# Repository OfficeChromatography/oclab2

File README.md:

# OCLab2
## Next Generation Office Chromatography

The former [OCLab prototype](https://github.com/OfficeChromatography/OCLab) of a “miniaturized all-in-one open
 source system for planar chromatography” was upgraded by an HPTLC plate visualizing cabinet to protect the 
 plate from extraneous light during capturing of images, including RGBW, UV 278 nm and UV 366 nm LED boards 
 as well as a Raspberry Pi V2 camera module. 
 
 Additionally, a newly designed printhead was manufactured, 
 controlled by a self-constructed ink-jet board allowing to check the nozzles’ resistance heating circuit. 
 Furthermore, plate heating was enabled, especially favorable when higher volumes of aqueous samples are to 
 be applied. 
 
 The former [OC Manager software](https://github.com/OfficeChromatography/OC_manager) was completely 
 restructured and newly written in R to speed-up the processes ([OC_manager2](https://github.com/OfficeChromatography/oc_manager2))
 , also supported by the new Raspberry Pi 4B computer with 4 GB RAM .

### Hardware/Firmware
The 3D printed parts are in the folder 'Construction Set', the electronic boards are described in the folder 
'Eagle Files', and the modified firmware is available in the folder 'Marlin'.
Assembly instructions are in the folder 'Instruction'.

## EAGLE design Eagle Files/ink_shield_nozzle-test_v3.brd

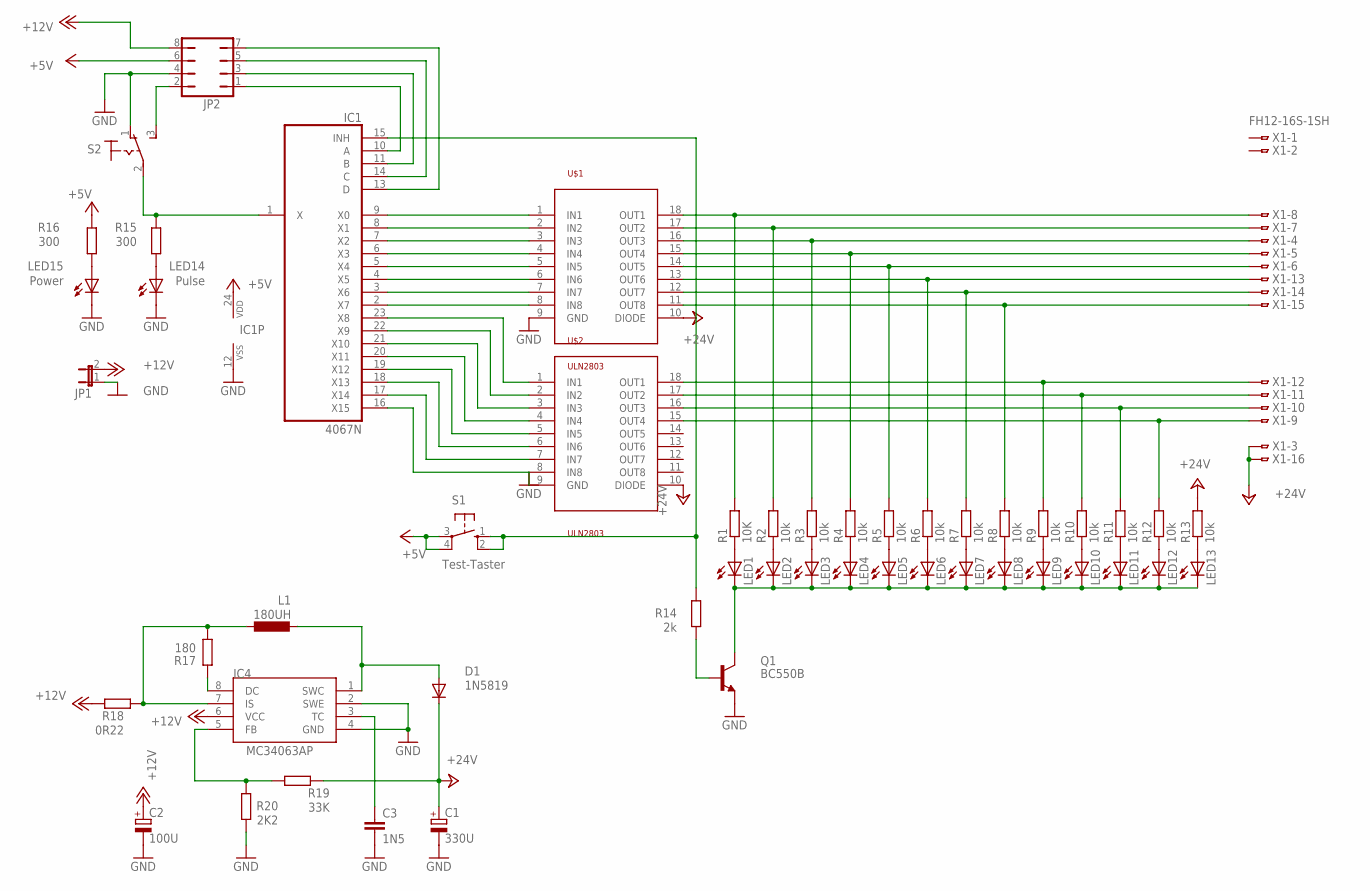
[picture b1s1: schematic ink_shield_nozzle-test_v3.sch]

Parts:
C1: 330U; E3,5-10
C2: 100U; E2,5-6
C3: 1N5; C025-024X044
D1: 1N5819; DO35-10
IC1: 4067N; DIL24-6
IC4: MC34063AP; DIL08
JP1: JP1E; JP1
JP2: JP4Q
L1: 180UH; 6000-XXXX-RC
LED1, LED2, LED3, LED4, LED5, LED6, LED7, LED8, LED9, LED10, LED11, LED12, LED13: LEDCHIPLED_0603; CHIPLED_0603
LED14: Pulse; LED3MM
LED15: Power; LED3MM
Q1: BC550B; TO92-EBC
R1: 10K; M1206
R2, R3, R4, R5, R6, R7, R8, R9, R10, R11, R12, R13: 10k; M1206
R14: 2k; M3216
R15, R16: 300; 0207/10
R17: 180; 0207/12
R18: 0R22; 0207/12
R19: 33K; 0207/12
R20: 2K2; 0207/10
S1: Test-Taster; B3F-10XX
S2: M9040P
U$1, U$2: ULN2803; SO18L
X1: FH12-16S-1SH

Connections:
+5V: IC1.24 (VDD), JP2.6, R16.2, S1.3, S1.4 (P1)
+12V: C2.+, IC4.6 (VCC), JP1.2, JP2.8, R18.2
+24V: C1.+, D1.C, R13.2, R19.1, U$1.10 (DIODE), U$2.10 (DIODE), X1.3, X1.16
GND: C1.-, C2.-, C3.2, IC1.12 (VSS), IC4.2 (SWE), IC4.4 (GND), JP1.1, JP2.4, LED14.K (C), LED15.K (C), Q1.E, R20.1, S2.1 (O), U$1.9 (GND), U$2.9 (GND)
unnamed: IC1.9 (X0), U$1.1 (IN1)
unnamed: IC1.8 (X1), U$1.2 (IN2)
unnamed: IC1.7 (X2), U$1.3 (IN3)
unnamed: IC1.6 (X3), U$1.4 (IN4)
unnamed: IC1.5 (X4), U$1.5 (IN5)
unnamed: IC1.4 (X5), U$1.6 (IN6)
unnamed: IC1.3 (X6), U$1.7 (IN7)
unnamed: IC1.2 (X7), U$1.8 (IN8)
unnamed: IC1.23 (X8), U$2.1 (IN1)
unnamed: IC1.22 (X9), U$2.2 (IN2)
unnamed: IC1.21 (X10), U$2.3 (IN3)
unnamed: IC1.20 (X11), U$2.4 (IN4)
unnamed: IC1.19 (X12), U$2.5 (IN5)
unnamed: IC1.18 (X13), U$2.6 (IN6)
unnamed: IC1.17 (X14), U$2.7 (IN7)
unnamed: IC1.16 (X15), U$2.8 (IN8)
unnamed: LED1.A, R1.1
unnamed: LED2.A, R2.1
unnamed: LED3.A, R3.1
unnamed: LED4.A, R4.1
unnamed: LED5.A, R5.1
unnamed: LED6.A, R6.1
unnamed: LED7.A, R7.1
unnamed: LED8.A, R8.1
unnamed: LED9.A, R9.1
unnamed: LED10.A, R10.1
unnamed: LED11.A, R11.1
unnamed: LED12.A, R12.1
unnamed: LED1.C, LED2.C, LED3.C, LED4.C, LED5.C, LED6.C, LED7.C, LED8.C, LED9.C, LED10.C, LED11.C, LED12.C, LED13.C, Q1.C
unnamed: R1.2, U$1.18 (OUT1), X1.8
unnamed: R2.2, U$1.17 (OUT2), X1.7
unnamed: R3.2, U$1.16 (OUT3), X1.4
unnamed: R4.2, U$1.15 (OUT4), X1.5
unnamed: R5.2, U$1.14 (OUT5), X1.6
unnamed: R6.2, U$1.13 (OUT6), X1.13
unnamed: R7.2, U$1.12 (OUT7), X1.14
unnamed: R8.2, U$1.11 (OUT8), X1.15
unnamed: R9.2, U$2.18 (OUT1), X1.12
unnamed: R10.2, U$2.17 (OUT2), X1.11
unnamed: R11.2, U$2.16 (OUT3), X1.10
unnamed: R12.2, U$2.15 (OUT4), X1.9
unnamed: LED13.A, R13.1
unnamed: IC1.15 (INH), R14.2, S1.1 (S), S1.2 (S1)
unnamed: Q1.B, R14.1
unnamed: LED14.A, R15.1
unnamed: IC1.10 (A), JP2.1
unnamed: IC1.11 (B), JP2.3
unnamed: IC1.14 (C), JP2.5
unnamed: IC1.13 (D), JP2.7
unnamed: IC1.1 (X), R15.2, S2.2
unnamed: LED15.A, R16.1
unnamed: IC4.7 (IS), L1.1, R17.2, R18.1
unnamed: D1.A, IC4.1 (SWC), L1.2
unnamed: IC4.8 (DC), R17.1
unnamed: C3.1, IC4.3 (TC)
unnamed: IC4.5 (FB), R19.2, R20.2
unnamed: JP2.2, S2.3 (S)

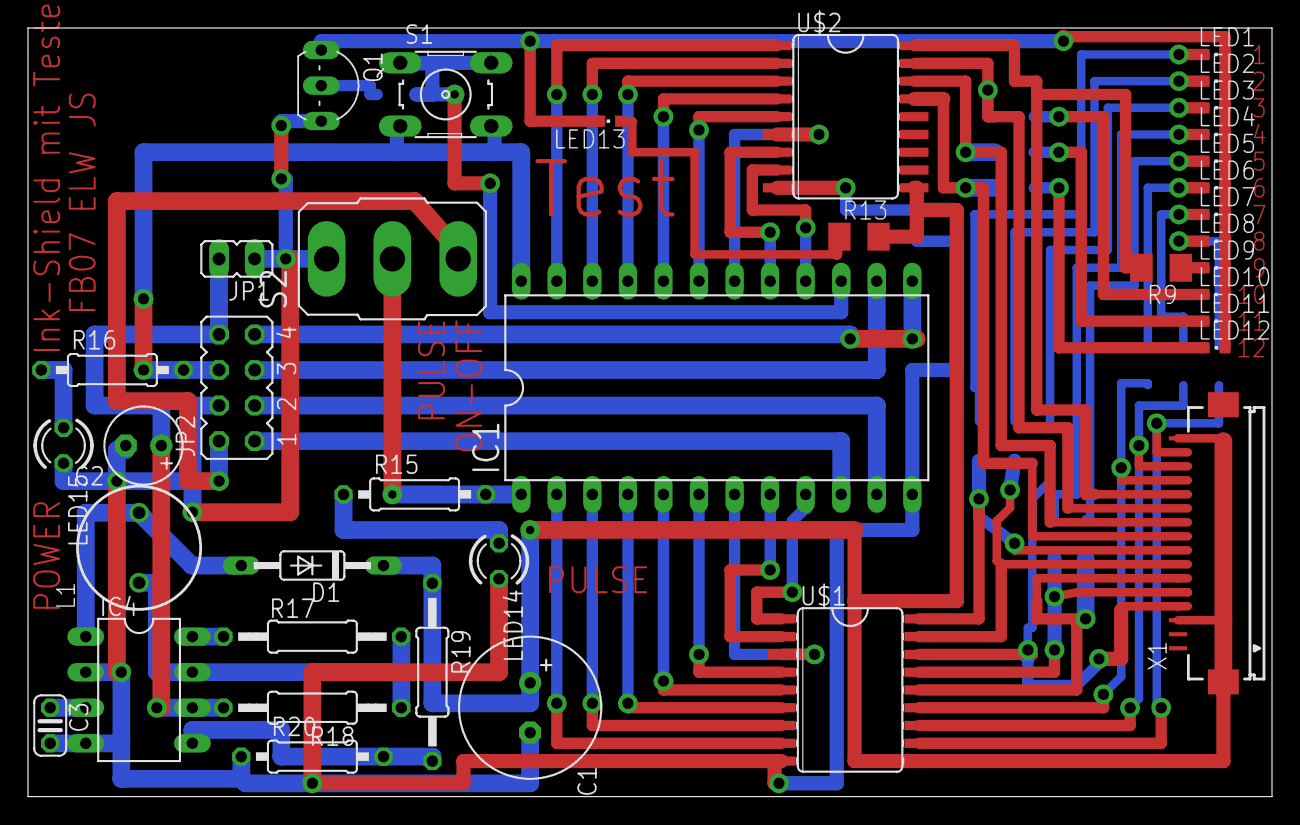
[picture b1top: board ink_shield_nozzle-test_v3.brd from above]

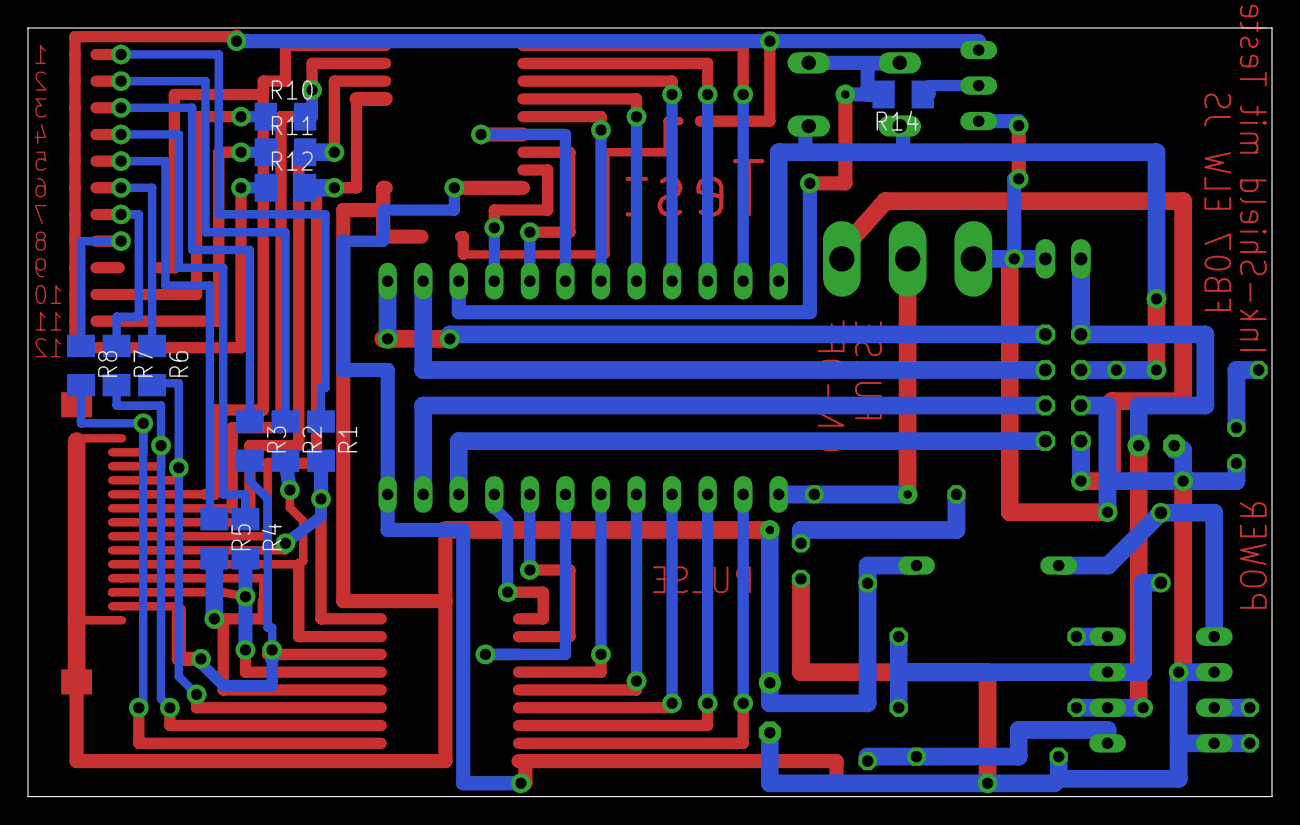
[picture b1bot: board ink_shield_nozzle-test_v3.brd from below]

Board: 2 copper layers, 88.9 x 54.9 mm, 50 parts (12 on the bottom side), 61 nets.

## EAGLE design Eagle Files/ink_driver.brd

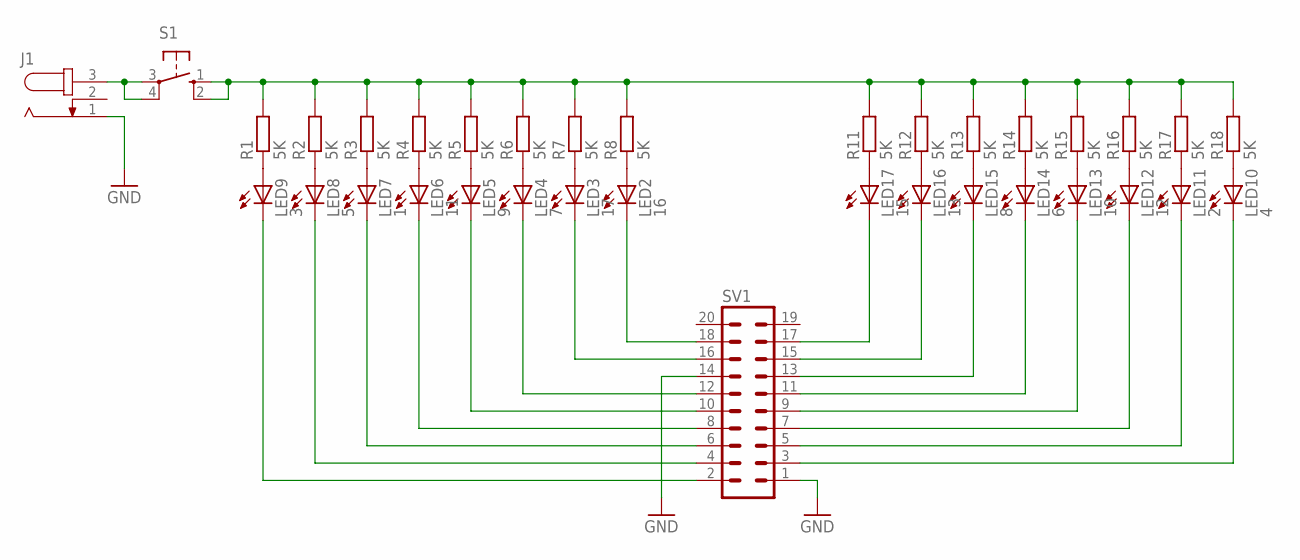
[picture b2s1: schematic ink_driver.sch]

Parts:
J1: JACK-PLUG1; SPC4078
LED2: 16; LED3MM
LED3: 17; LED3MM
LED4: 7; LED3MM
LED5: 9; LED3MM
LED6: 11; LED3MM
LED7: 1; LED3MM
LED8: 5; LED3MM
LED9: 3; LED3MM
LED10: 4; LED3MM
LED11: 2; LED3MM
LED12: 12; LED3MM
LED13: 10; LED3MM
LED14: 6; LED3MM
LED15: 8; LED3MM
LED16: 13; LED3MM
LED17: 15; LED3MM
R1, R2, R3, R4, R5, R6, R7, R8, R11, R12, R13, R14, R15, R16, R17, R18: 5K; 0207/10
S1: 10-XX; B3F-10XX
SV1: ML20

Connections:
GND: J1.1, SV1.1, SV1.14
unnamed: LED2.K (C), SV1.18
unnamed: LED3.K (C), SV1.16
unnamed: LED4.K (C), SV1.12
unnamed: LED5.K (C), SV1.10
unnamed: LED6.K (C), SV1.8
unnamed: LED7.K (C), SV1.6
unnamed: LED8.K (C), SV1.4
unnamed: LED9.K (C), SV1.2
unnamed: LED9.A, R1.1
unnamed: LED8.A, R2.1
unnamed: LED7.A, R3.1
unnamed: LED6.A, R4.1
unnamed: LED5.A, R5.1
unnamed: LED4.A, R6.1
unnamed: LED3.A, R7.1
unnamed: LED2.A, R8.1
unnamed: LED17.A, R11.1
unnamed: LED16.A, R12.1
unnamed: LED15.A, R13.1
unnamed: LED14.A, R14.1
unnamed: LED13.A, R15.1
unnamed: LED12.A, R16.1
unnamed: LED11.A, R17.1
unnamed: LED10.A, R18.1
unnamed: LED17.K (C), SV1.17
unnamed: LED16.K (C), SV1.15
unnamed: LED15.K (C), SV1.13
unnamed: LED14.K (C), SV1.11
unnamed: LED13.K (C), SV1.9
unnamed: LED12.K (C), SV1.7
unnamed: LED11.K (C), SV1.5
unnamed: LED10.K (C), SV1.3
unnamed: R1.2, R2.2, R3.2, R4.2, R5.2, R6.2, R7.2, R8.2, R11.2, R12.2, R13.2, R14.2, R15.2, R16.2, R17.2, R18.2, S1.1 (S), S1.2 (S1)
unnamed: J1.3, S1.3, S1.4 (P1)

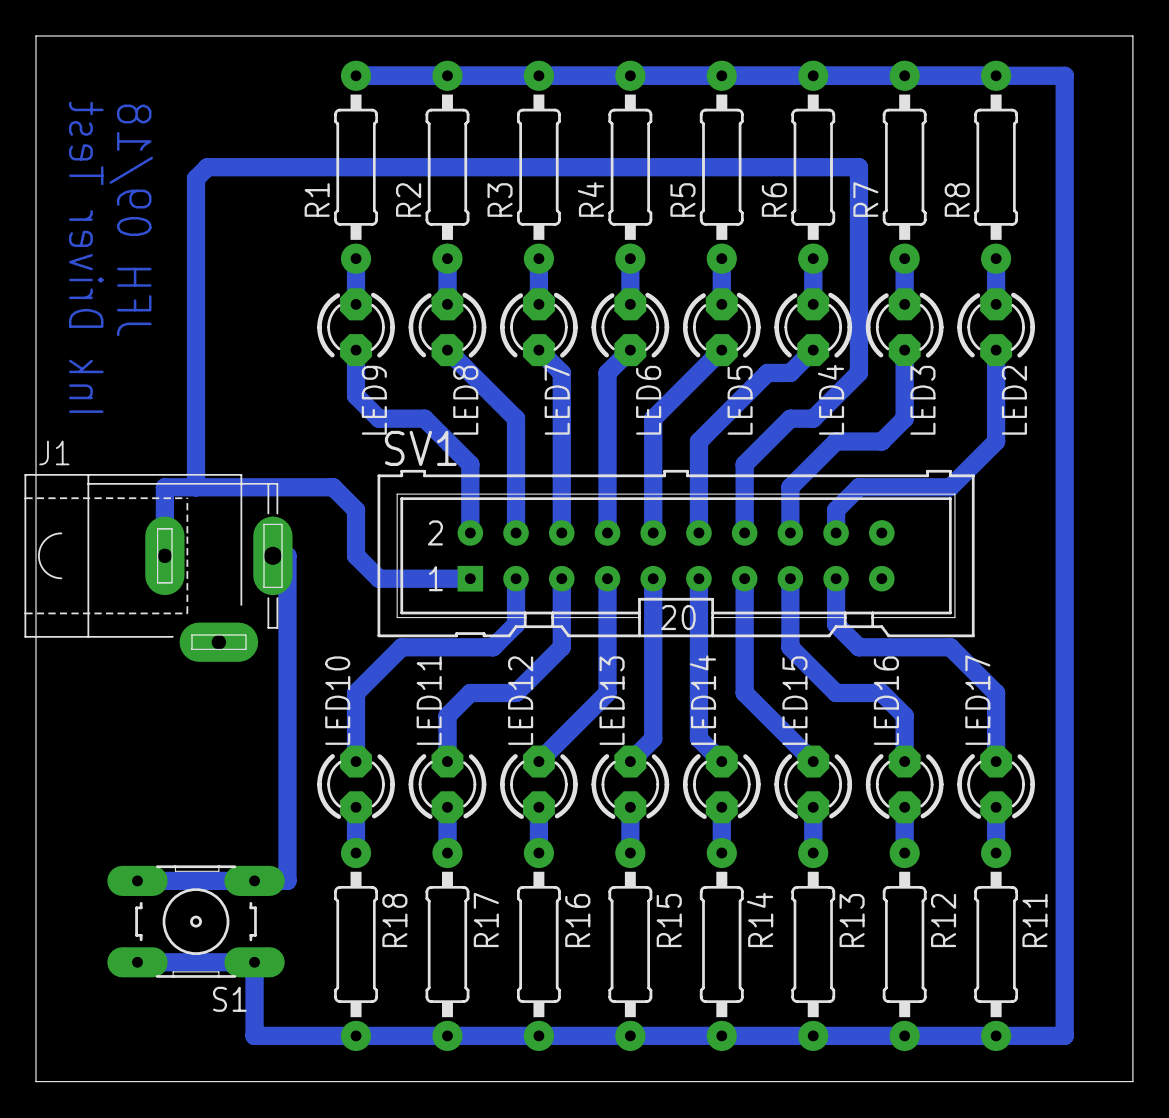
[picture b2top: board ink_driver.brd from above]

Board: 2 copper layers, 60.9 x 58.1 mm, 35 parts (0 on the bottom side), 35 nets.

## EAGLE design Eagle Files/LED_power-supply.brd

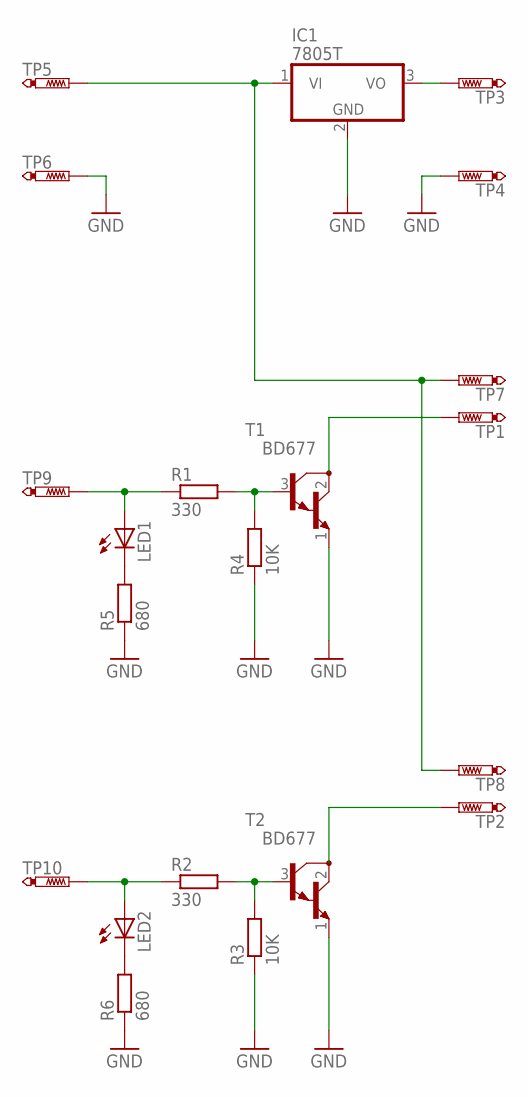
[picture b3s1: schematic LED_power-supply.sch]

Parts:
IC1: 7805T; TO220H
LED1, LED2: LED3MM
R1, R2: 330; 0207/10
R3, R4: 10K; 0207/10
R5, R6: 680; 0207/10
T1, T2: BD677; TO126
TP1, TP2, TP3, TP4, TP5, TP6, TP7, TP8, TP9, TP10: PTR1PAD1-17; P1-17

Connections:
GND: IC1.2 (GND), R3.1, R4.1, R5.1, R6.1, T1.1 (E), T2.1 (E), TP4.TP, TP6.TP
unnamed: R1.2, R4.2, T1.3 (B)
unnamed: LED1.A, R1.1, TP9.TP
unnamed: T1.2 (C), TP1.TP
unnamed: R2.2, R3.2, T2.3 (B)
unnamed: LED2.A, R2.1, TP10.TP
unnamed: T2.2 (C), TP2.TP
unnamed: IC1.3 (VO), TP3.TP
unnamed: LED1.K (C), R5.2
unnamed: IC1.1 (VI), TP5.TP, TP7.TP, TP8.TP
unnamed: LED2.K (C), R6.2

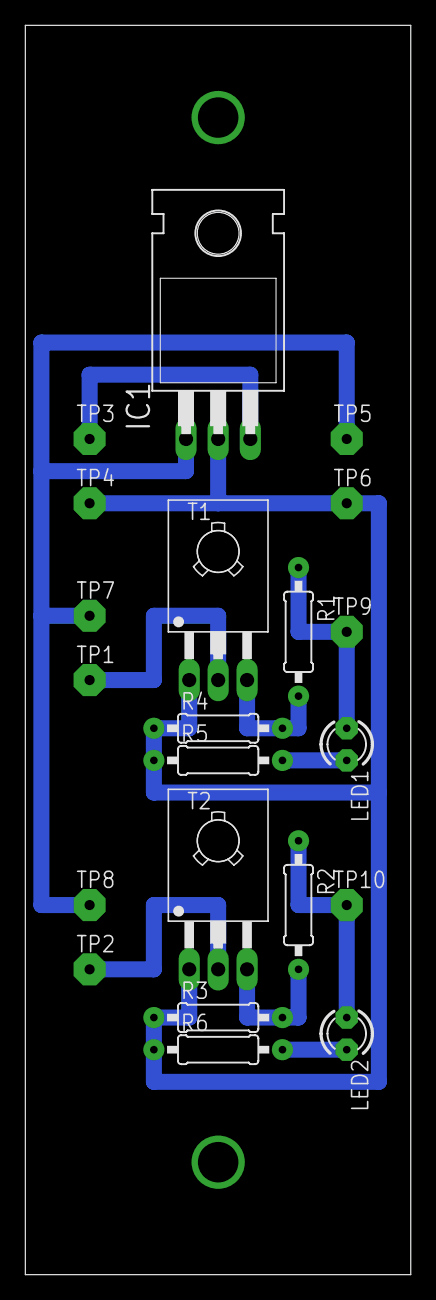
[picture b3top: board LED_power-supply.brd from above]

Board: 2 copper layers, 30.5 x 98.7 mm, 21 parts (0 on the bottom side), 11 nets.

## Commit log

2021-04-08 Readme updated
2021-04-08 corrections
2021-04-09 eagle files added
2021-12-25 Eagle files new
